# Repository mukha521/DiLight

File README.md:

# DiLight

### Простой светильник с плавным включением и выключением света с датчиком расстояния vl53l0x от ST на базе STM32G030

[Код main()](/firmware/Core/Src/main.c)

[Драйвер vl53l0x](/firmware/Drivers/vl53l0x/)

При долгом удержании пальца на тач-кнопке, включается режим конфигурирования.
Нужно встать на расстоянии, где светильник будет включаться и тапнуть по кнопке.
Затем встать на расстоянии, где светильник будет отключаться и тапнуть по кнопке.
Конфигурация хранится на последней странице флеш-памяти контроллера.

Светильник включается если человек (или что-то другое) приближается на растояние, установленное при конфигурировании и выключается как только человек удаляется на расстояние большее, чем рысстояние выключения.
Тап по кнопке по кругу переключает ражимы работы светильника: Нормальный -> Всегда включен -> Всегда выключен.

[Схема rev.2.0](/kicad/rev.2.0/DiLight_2.0.pdf)

[Интерактивный BOM-лист](/kicad/rev.2.0/bom/)

В устройстве есть защита от переполюсовки птания (подключение с обратной полярностью), но нет защиты от превышения напряжения (12v) и от короткого замыкания по нагрузке. Целью была миниатюризация устройства.

#### Фото реального устройства:

#### Видео с демонстрацией работы:

(кликнуть по изображению - ссылка на YouTube)

#### История:

rev.2.0a:
- Исправлена маркировка +/- для терминала LEDs

rev.2.0:
- Уменьшен размер платы
- Использован менее мощный MOSFET в корпусе SOT-23
- Убраны ограничивающие резисторы с разъемов
- Убрана разводка UART на разъем программирования
- Только один терминал для подключения ленты
- Плата с корпусом теперь надевается на профиль для ленты. Не нужно разрезать профиль.

rev.1.1
- винтовой терминал вместо "бочко-разъема" для шнура питания
- MOSFET вместо диода в качестве защиты от обратной полярности питания

#### Рендер платы:
rev.2.0a:

rev.2.0:

rev.1.1:

#### Рендер устройства:

#### Промежуточные фото платы (флюс не отмыт :) )

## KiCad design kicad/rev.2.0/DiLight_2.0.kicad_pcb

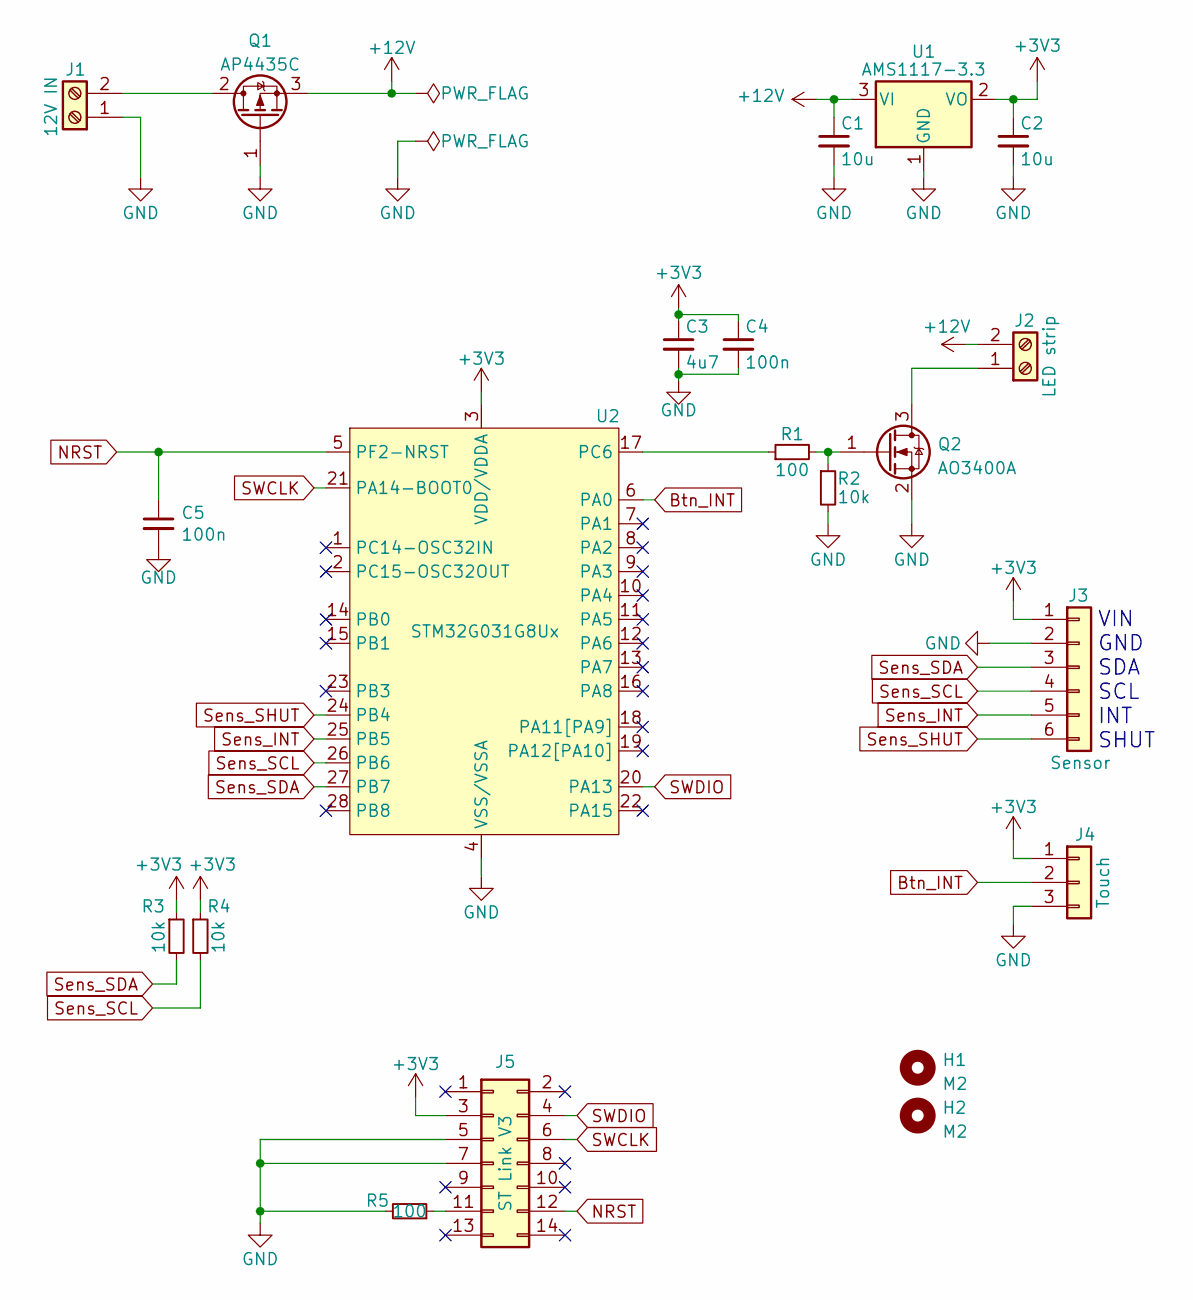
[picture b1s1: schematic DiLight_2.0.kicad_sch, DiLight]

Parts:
C1, C2: 10u; C_0805_2012Metric_Pad1.18x1.45mm_HandSolder
C3: 4u7; C_0805_2012Metric_Pad1.18x1.45mm_HandSolder
C4, C5: 100n; C_0805_2012Metric_Pad1.18x1.45mm_HandSolder
H1, H2: M2; MountingHole_2.2mm_M2_DIN965
J1: 12V IN; TerminalBlock_Phoenix_PT-1,5-2-5.0-H_1x02_P5.00mm_Horizontal
J2: LED strip; TerminalBlock_Phoenix_PT-1,5-2-5.0-H_1x02_P5.00mm_Horizontal
J3: Sensor; PinHeader_1x06_P2.54mm_Vertical
J4: Touch; PinHeader_1x03_P2.54mm_Vertical
J5: ST Link V3; PinHeader_2x07_P1.27mm_Vertical_SMD
Q1: AP4435C; SOP-8_PMOS_GDS
Q2: AO3400A; SOT-23_Handsoldering
R1, R5: 100; R_0805_2012Metric_Pad1.20x1.40mm_HandSolder
R2, R3, R4: 10k; R_0805_2012Metric_Pad1.20x1.40mm_HandSolder
U1: AMS1117-3.3; SOT-223-3_TabPin2
U2: STM32G031G8Ux; QFN-28_4x4mm_P0.5mm

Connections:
+3V3: C2.1, C3.1, C4.1, J3.1, J4.1, J5.3, R3.1, R4.1, U1.2 (VO), U2.3 (VDD/VDDA)
+12V: C1.1, J2.2, Q1.3 (S), U1.3 (VI)
Btn_INT: J4.2, U2.6 (PA0)
GND: C1.2, C2.2, C3.2, C4.2, C5.2, J1.1, J3.2, J4.3, J5.5, J5.7, Q1.1 (G), Q2.2 (S), R2.2, R5.2, U1.1 (GND), U2.4 (VSS/VSSA)
NRST: C5.1, J5.12, U2.5 (PF2-NRST)
unnamed: J1.2, Q1.2 (D)
unnamed: J2.1, Q2.3 (D)
unnamed: J5.11, R5.1
unnamed: Q2.1 (G), R1.2, R2.1
unnamed: R1.1, U2.17 (PC6)
SWCLK: J5.6, U2.21 (PA14-BOOT0)
SWDIO: J5.4, U2.20 (PA13)
Sens_INT: J3.5, U2.25 (PB5)
Sens_SCL: J3.4, R4.2, U2.26 (PB6)
Sens_SDA: J3.3, R3.2, U2.27 (PB7)
Sens_SHUT: J3.6, U2.24 (PB4)

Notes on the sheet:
VIN GND SDA SCL INT SHUT

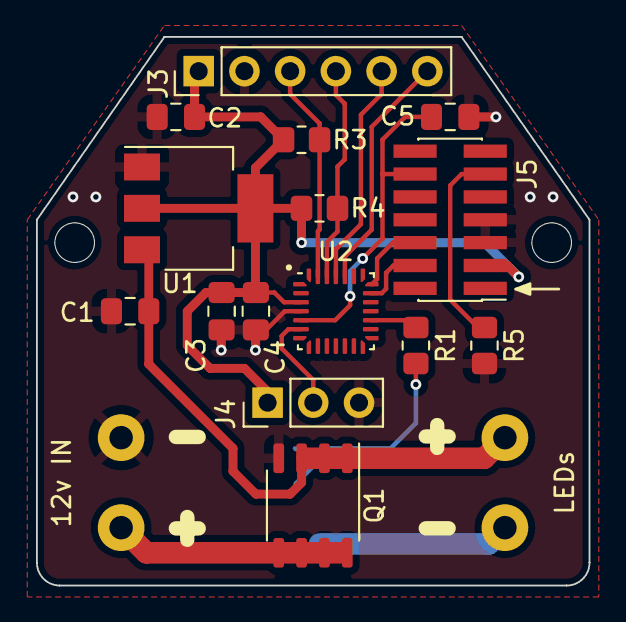
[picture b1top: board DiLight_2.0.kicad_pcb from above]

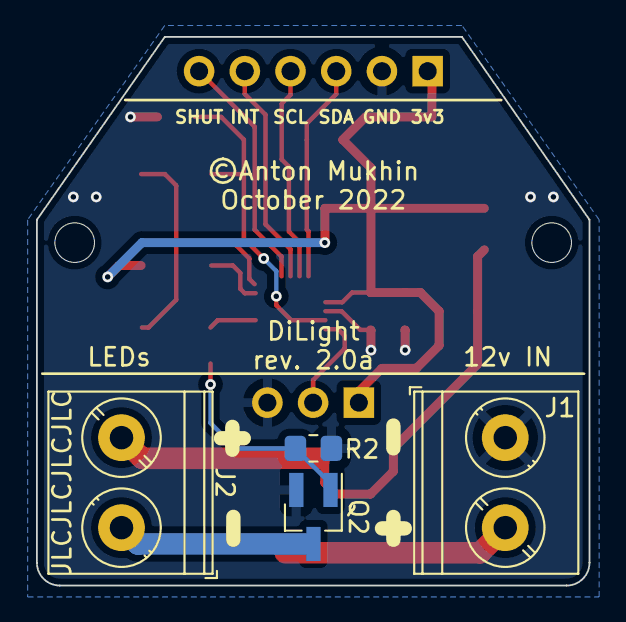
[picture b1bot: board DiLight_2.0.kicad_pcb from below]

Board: 2 copper layers, 30.7 x 30.5 mm, 21 parts (4 on the bottom side), 16 nets.

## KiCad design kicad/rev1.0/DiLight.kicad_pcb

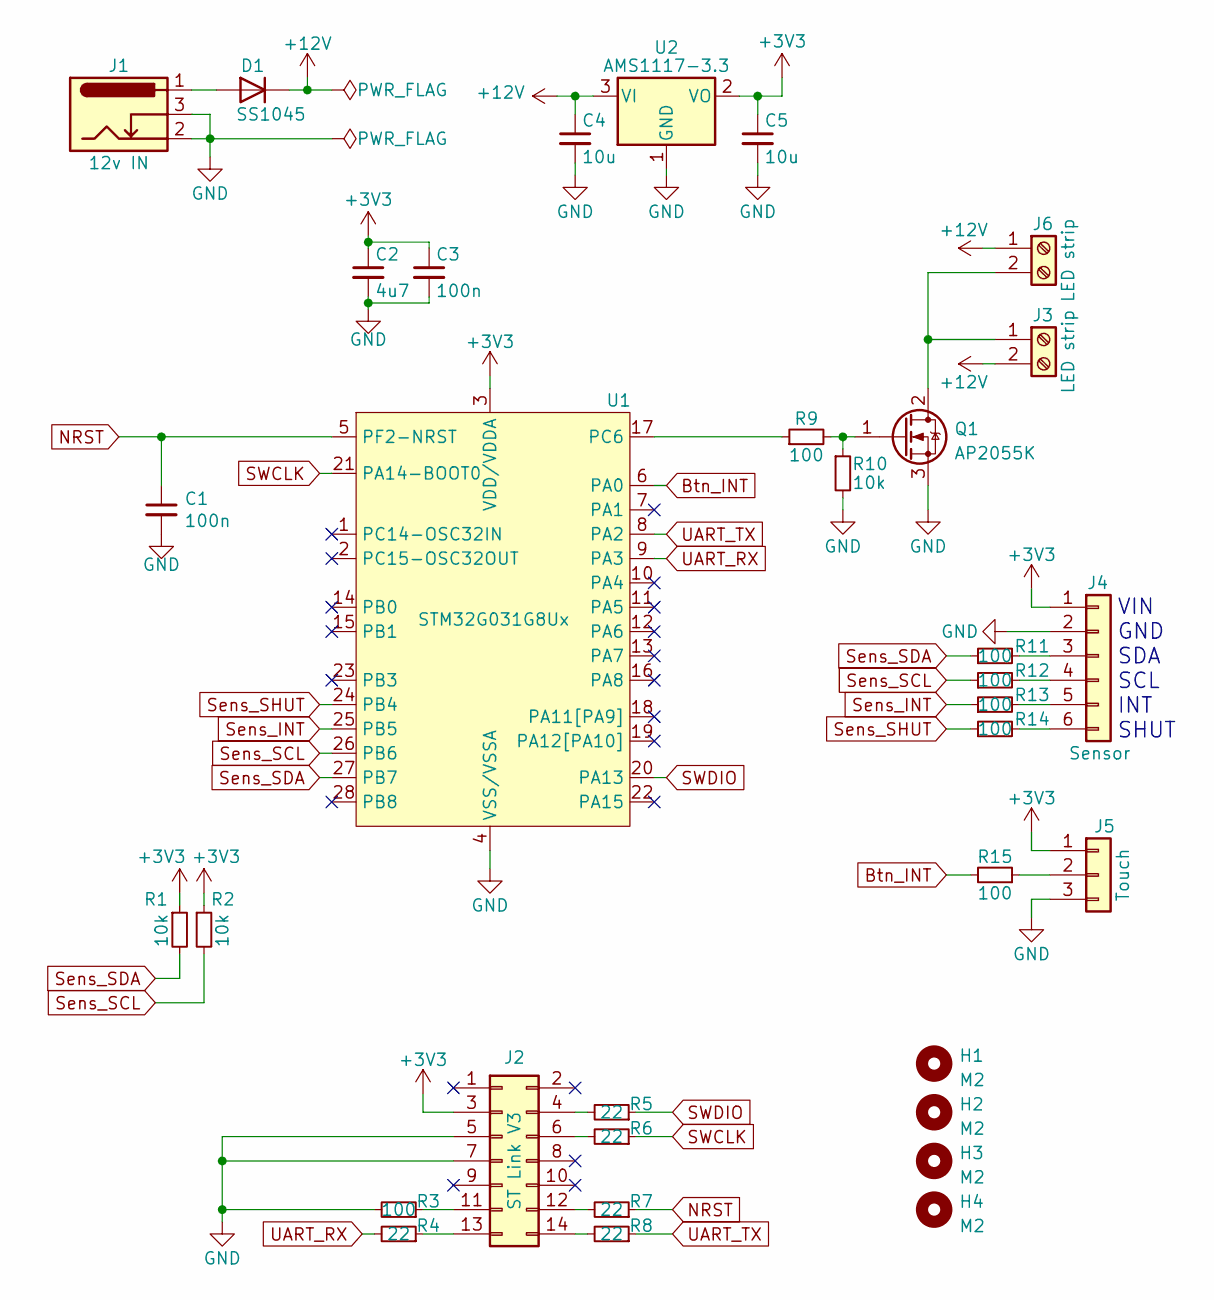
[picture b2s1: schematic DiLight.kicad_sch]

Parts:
C1, C3: 100n; C_0805_2012Metric_Pad1.18x1.45mm_HandSolder
C2: 4u7; C_0805_2012Metric_Pad1.18x1.45mm_HandSolder
C4, C5: 10u; C_0805_2012Metric_Pad1.18x1.45mm_HandSolder
D1: SS1045; D_SMB-SMC_Universal_Handsoldering
H1, H2, H3, H4: M2; MountingHole_2.2mm_M2_DIN965
J1: 12v IN; BarrelJack_Horizontal
J2: ST Link V3; PinHeader_2x07_P1.27mm_Vertical_SMD
J3, J6: LED strip; TerminalBlock_Phoenix_PT-1,5-2-5.0-H_1x02_P5.00mm_Horizontal
J4: Sensor; PinHeader_1x06_P2.54mm_Vertical
J5: Touch; PinHeader_1x03_P2.54mm_Vertical
Q1: AP2055K; TO-252-2
R1, R2, R10: 10k; R_0805_2012Metric_Pad1.20x1.40mm_HandSolder
R3, R9, R11, R12, R13, R14, R15: 100; R_0805_2012Metric_Pad1.20x1.40mm_HandSolder
R4, R5, R6, R7, R8: 22; R_0805_2012Metric_Pad1.20x1.40mm_HandSolder
U1: STM32G031G8Ux; QFN-28_4x4mm_P0.5mm
U2: AMS1117-3.3; SOT-223-3_TabPin2

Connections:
+3V3: C2.1, C3.1, C5.1, J2.3, J4.1, J5.1, R1.1, R2.1, U1.3 (VDD/VDDA), U2.2 (VO)
+12V: C4.1, D1.1 (K), J3.2, J6.1, U2.3 (VI)
Btn_INT: R15.2, U1.6 (PA0)
GND: C1.2, C2.2, C3.2, C4.2, C5.2, J1.2, J1.3, J2.5, J2.7, J4.2, J5.3, Q1.3 (S), R3.2, R10.2, U1.4 (VSS/VSSA), U2.1 (GND)
NRST: C1.1, R7.1, U1.5 (PF2-NRST)
unnamed: D1.2 (A), J1.1
unnamed: J2.4, R5.2
unnamed: J2.6, R6.2
unnamed: J2.11, R3.1
unnamed: J2.12, R7.2
unnamed: J2.13, R4.1
unnamed: J2.14, R8.2
unnamed: J5.2, R15.1
unnamed: J3.1, J6.2, Q1.2 (D)
unnamed: R9.1, U1.17 (PC6)
unnamed: Q1.1 (G), R9.2, R10.1
unnamed: J4.3, R11.2
unnamed: J4.4, R12.2
unnamed: J4.5, R13.2
unnamed: J4.6, R14.2
SWCLK: R6.1, U1.21 (PA14-BOOT0)
SWDIO: R5.1, U1.20 (PA13)
Sens_INT: R13.1, U1.25 (PB5)
Sens_SCL: R2.2, R12.1, U1.26 (PB6)
Sens_SDA: R1.2, R11.1, U1.27 (PB7)
Sens_SHUT: R14.1, U1.24 (PB4)
UART_RX: R4.2, U1.9 (PA3)
UART_TX: R8.1, U1.8 (PA2)

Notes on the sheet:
VIN GND SDA SCL INT SHUT

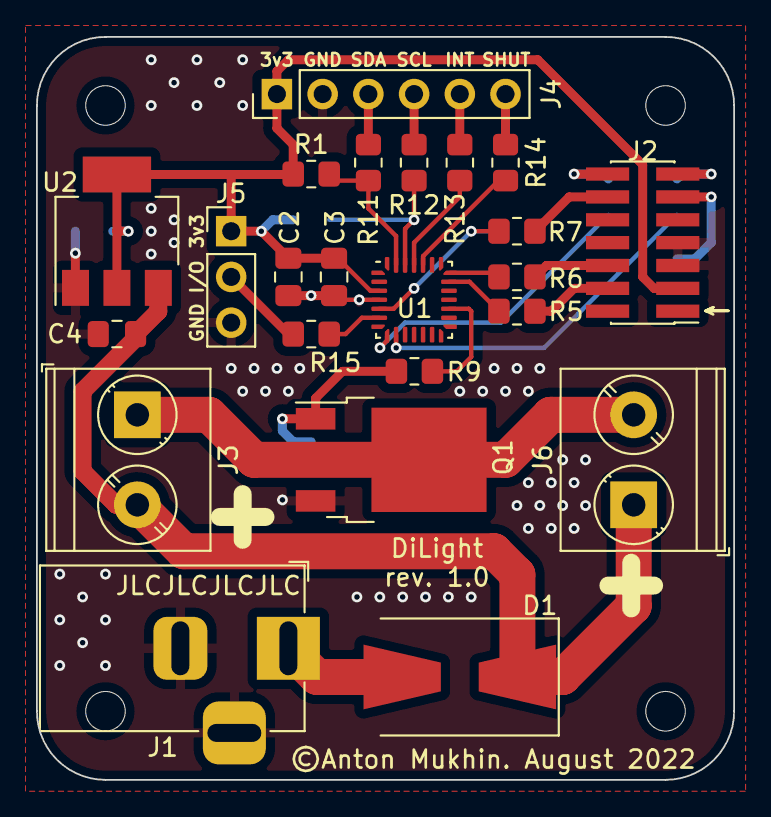
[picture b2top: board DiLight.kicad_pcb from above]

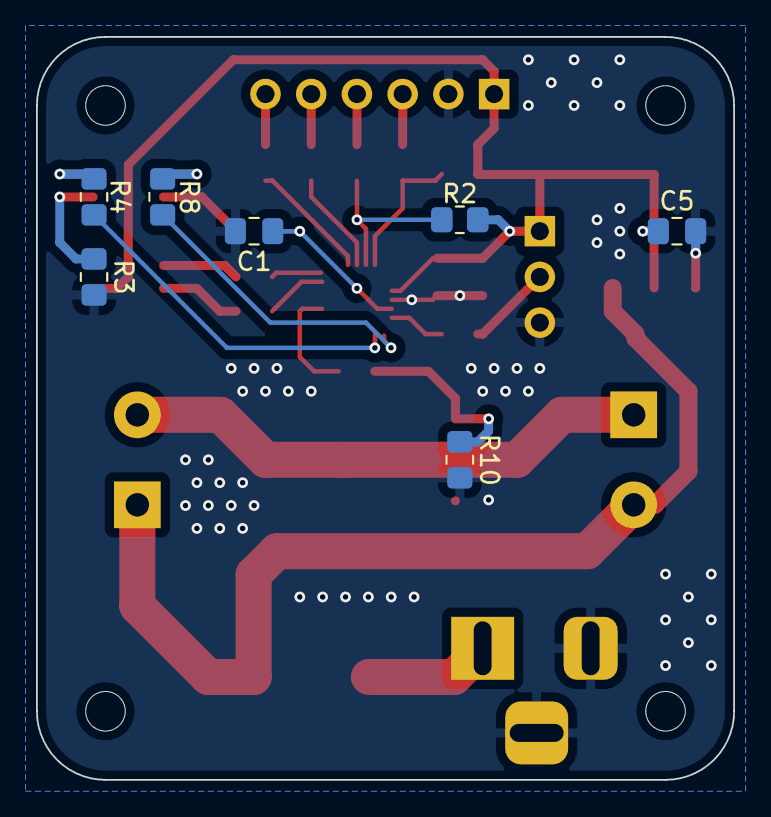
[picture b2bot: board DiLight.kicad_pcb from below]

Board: 2 copper layers, 38.7 x 41.3 mm, 34 parts (7 on the bottom side), 28 nets.

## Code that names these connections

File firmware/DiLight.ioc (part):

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Mcu.Name=STM32G031G(4-6-8)Ux
Mcu.Package=UFQFPN28
Mcu.UserName=STM32G031G8Ux
PA0.GPIOParameters=GPIO_Label,GPIO_ModeDefaultEXTI
PA0.GPIO_Label=Btn_INT
PA0.GPIO_ModeDefaultEXTI=GPIO_MODE_IT_RISING_FALLING
PA0.Signal=GPXTI0
PA13.Mode=Serial_Wire
PA13.Signal=SYS_SWDIO
PA14-BOOT0.Mode=Serial_Wire
PA14-BOOT0.Signal=SYS_SWCLK
PB4.GPIOParameters=GPIO_Speed,PinState,GPIO_PuPd,GPIO_Label
PB4.GPIO_Label=Sens_SHUT
PB4.GPIO_PuPd=GPIO_PULLUP
PB4.GPIO_Speed=GPIO_SPEED_FREQ_HIGH
PB4.PinState=GPIO_PIN_SET
PB4.Signal=GPIO_Output
PB5.GPIOParameters=GPIO_Label,GPIO_ModeDefaultEXTI
PB5.GPIO_Label=Sens_INT
PB5.GPIO_ModeDefaultEXTI=GPIO_MODE_IT_FALLING
PB5.Signal=GPXTI5
PB6.GPIOParameters=GPIO_Label
PB6.GPIO_Label=Sens_SCL
PB6.Mode=I2C
PB6.Signal=I2C1_SCL
PB7.GPIOParameters=GPIO_Label
PB7.GPIO_Label=Sens_SDA
PB7.Mode=I2C
PB7.Signal=I2C1_SDA
PC6.Signal=S_TIM3_CH1
RCC.HSE_VALUE=8000000
RCC.SYSCLKFreq_VALUE=64000000
RCC.SYSCLKSource=RCC_SYSCLKSOURCE_PLLCLK
board=custom

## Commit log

2022-11-14 tabspace fix. minor changes.
2022-11-23 PCB silkscreen +/- marks positions fixed. Manual on/off still works if the range sensor is not initialized
2022-11-30 .gitignore file
2022-11-30 .gitignore file change
2022-11-30 Removed compiled files
2022-11-30 Configured distance values are checked before saved.
2022-11-30 kicad backups removed
2022-11-30 .gitignore amended
2022-11-30 more kicad backups removed
2022-11-30 BOM status changed for some components. iBOM regenerated
2022-11-30 New rev.2.0a PCB renders
2022-11-30 Generated new gerbers for rev.2.0a
2022-11-30 new device render
2022-11-30 Assembly STEP file added
2022-11-30 .editorconfig file added
2022-12-01 photos added
2022-12-01 more photos
2023-01-20 Reworked light modes; now there are 3 modes cycled by a button taps - normal, manual on, manual off.
2023-01-21 Moved modeswitch logic out of the ISR handler; Fixed fade in/out logic so it wont turn on the light when asked to fade out;
2023-01-21 Tidy up the code
2023-01-21 README.md change
2023-01-25 Memory regions described in the ld file

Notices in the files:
kicad/rev.2.0/DiLight_2.0.kicad_pcb:
©Anton Mukhin
kicad/rev1.0/DiLight.kicad_pcb:
©Anton Mukhin. August 2022
